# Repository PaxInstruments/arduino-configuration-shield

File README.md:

# Pax Instruments
# Arduino Configuration Shield

[Pax Instruments Template Module](<link to store page>)

## Overview
The Pax Instruments Arduino Configuration Shield is an Arduino shield for the Pax Instruments LCD23164 graphic LCD. You can [purchase this item in our store](http://paxinstruments.com/products/sku1003/).

## Repository Contents
- __Datasheets__ - Datasheets for relevant components and parts
- __Electronics__ - All PCB and schematic design files
- __Enclosure__ - Enclosure 3D design files
- __Firmware__ - Firmware, libraries, and examples
- __Production__ - Manufacturing resources
- __Resources__ - Other resources

## Product Versions

## License Information
```
Place the license statement here
```

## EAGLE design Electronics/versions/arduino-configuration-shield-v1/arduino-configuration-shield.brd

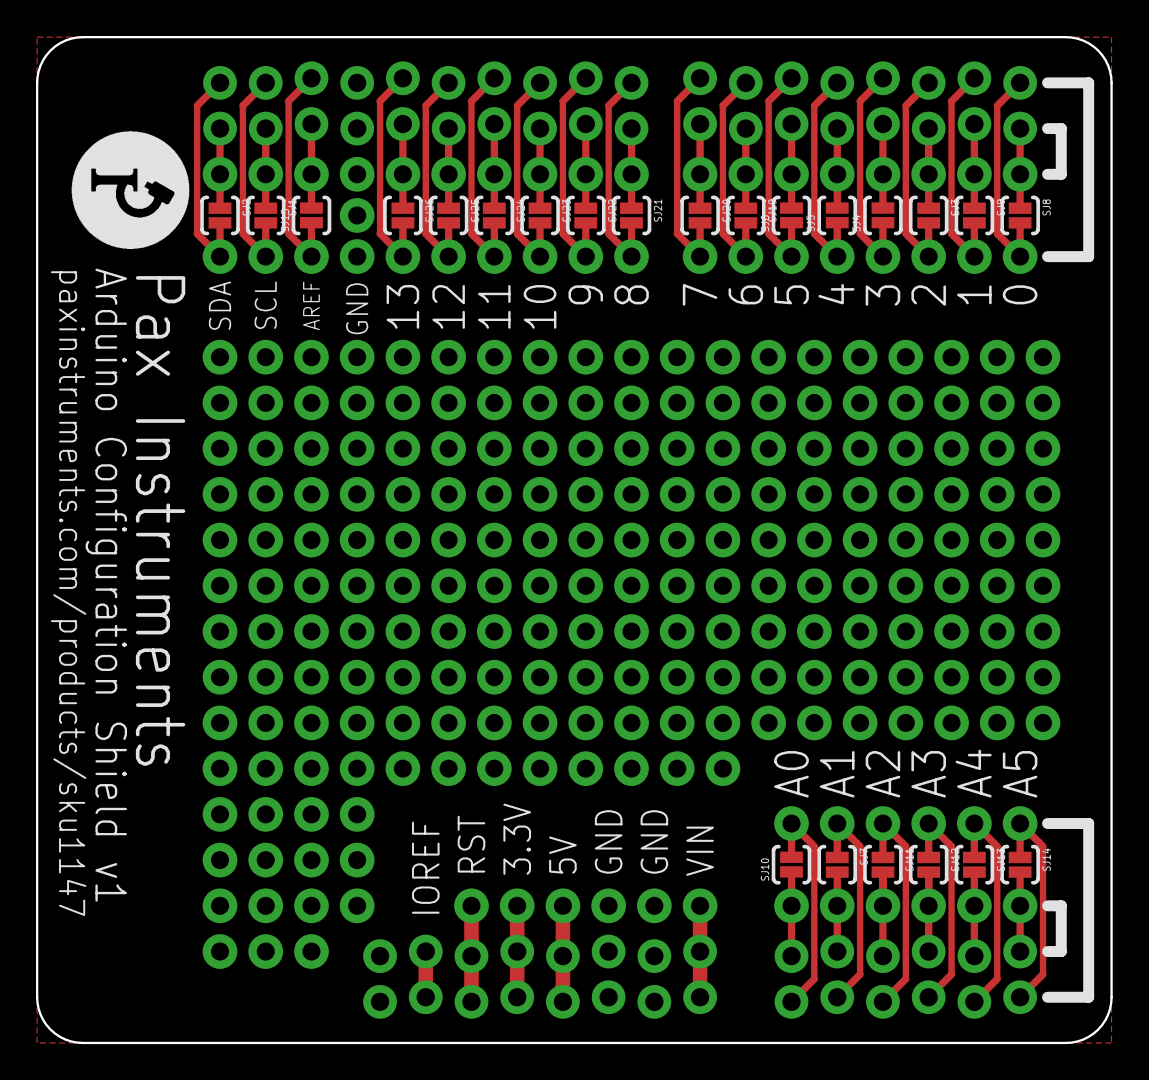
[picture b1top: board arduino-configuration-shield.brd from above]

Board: 2 copper layers, 59.7 x 55.9 mm, 27 parts (1 on the bottom side), 29 nets.

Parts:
J1, J3: ARDUINO_R3_SHIELDUNO_R3_SHIELD_NOLABELS_LOCK; UNO_R3_SHIELD_NOLABELS_LOCK
SJ1, SJ2, SJ3, SJ4, SJ5, SJ6, SJ7, SJ8, SJ9, SJ10, SJ11, SJ12, SJ13, SJ14, SJ15, SJ19, SJ20, SJ21, SJ22, SJ23, SJ24, SJ25, SJ26: JUMPER-PAD-2-NC_BY_PASTE; PAD-JUMPER-2-NC_BY_PASTE_YES_SILK
U$1, U$6: PAXINSTRUMENT_LOGO

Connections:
3.3V: J1.3.3V, J3.3.3V
5V: J1.5V, J3.5V
A0: J1.A0, J3.A0, SJ10.1, SJ10.2
A1: J1.A1, J3.A1, SJ7.1, SJ7.2
A2: J1.A2, J3.A2, SJ11.1, SJ11.2
A3: J1.A3, J3.A3, SJ12.1, SJ12.2
A4: J1.A4, J3.A4, SJ13.1, SJ13.2
A5: J1.A5, J3.A5, SJ14.1, SJ14.2
AREF: J1.AREF, J3.AREF, SJ15.1, SJ15.2
D0: J1.RX, J3.RX, SJ8.1, SJ8.2
D1: J1.TX, J3.TX, SJ9.1, SJ9.2
D2: J1.D2, J3.D2, SJ3.1, SJ3.2
D3: J1.D3, J3.D3, SJ4.1, SJ4.2
D4: J1.D4, J3.D4, SJ5.1, SJ5.2
D5: J1.D5, J3.D5, SJ6.1, SJ6.2
D6: J1.D6, J3.D6, SJ19.1, SJ19.2
D7: J1.D7, J3.D7, SJ20.1, SJ20.2
D8: J1.D8, J3.D8, SJ21.1, SJ21.2
D9: J1.D9, J3.D9, SJ22.1, SJ22.2
D10: J1.D10, J3.D10, SJ23.1, SJ23.2
D11(MOSI): J1.D11, J3.D11, SJ24.1, SJ24.2
D12(MISO): J1.D12, J3.D12, SJ25.1, SJ25.2
D13(SCK): J1.D13, J3.D13, SJ26.1, SJ26.2
GND: J1.GND@0, J1.GND@1, J1.GND@2, J3.GND@0, J3.GND@1, J3.GND@2
IOREF: J1.IOREF, J3.IOREF
RESET: J1.RES, J3.RES
SCL: J1.SCL, J3.SCL, SJ2.1, SJ2.2
SDA: J1.SDA, J3.SDA, SJ1.1, SJ1.2
VIN: J1.VIN, J3.VIN

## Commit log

2015-05-09 Added PCB and other files.
2015-05-09 Added v1 gerbers and version files.

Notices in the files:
parts and their libraries:
SparkFun-Boards: Licensing: Creative Commons ShareAlike 4.0 International - https://creativecommons.org/licenses/by-sa/4.0
